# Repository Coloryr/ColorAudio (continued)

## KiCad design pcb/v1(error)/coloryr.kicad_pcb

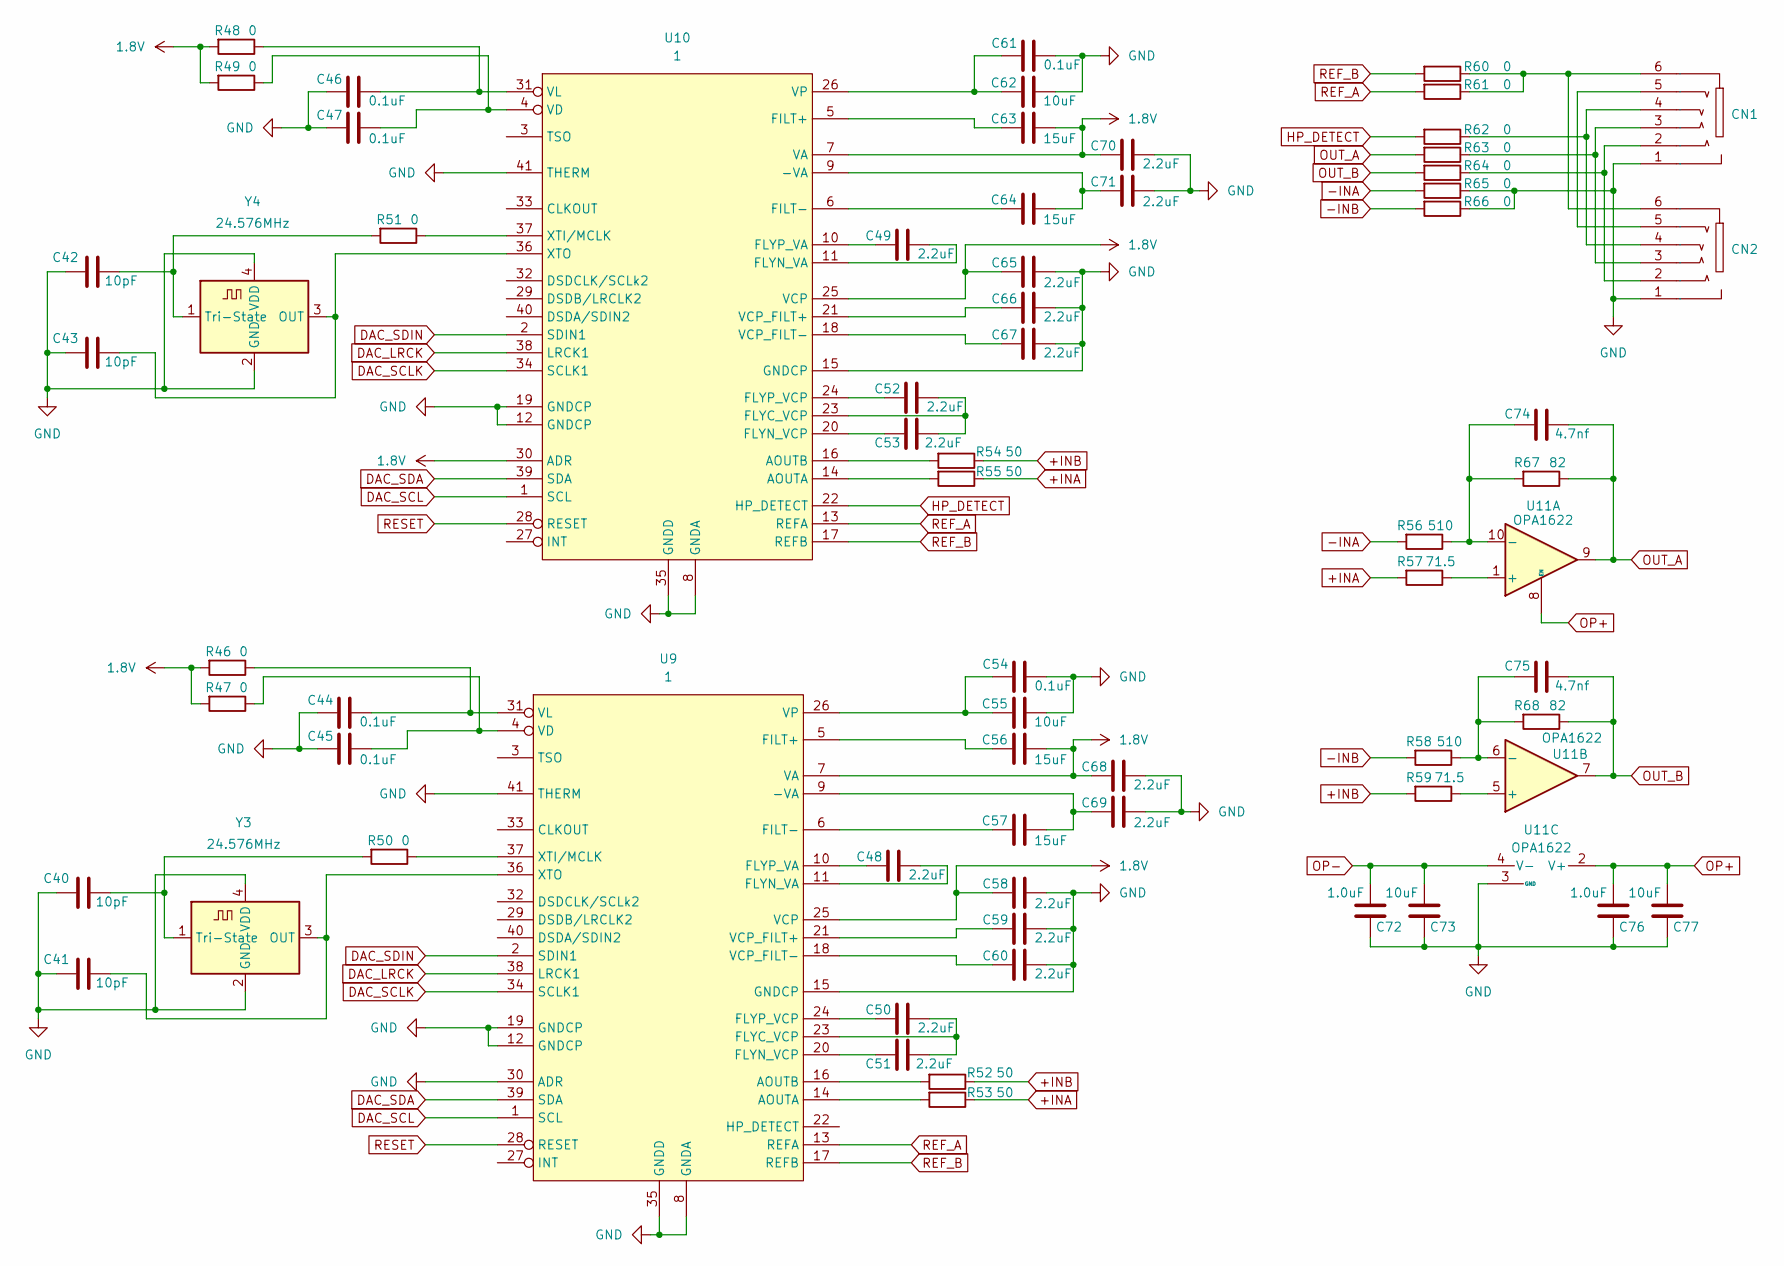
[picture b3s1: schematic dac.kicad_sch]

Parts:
C40, C41, C42, C43: 10pF; C_0402_1005Metric_Pad0.74x0.62mm_HandSolder
C44, C45, C46, C47, C54, C61: 0.1uF; C_0402_1005Metric_Pad0.74x0.62mm_HandSolder
C48, C49, C50, C51, C52, C53, C58, C59, C60, C65, C66, C67, C68, C69, C70, C71: 2.2uF; C_0402_1005Metric_Pad0.74x0.62mm_HandSolder
C55, C62, C73, C77: 10uF; C_0402_1005Metric_Pad0.74x0.62mm_HandSolder
C56, C57, C63, C64: 15uF; C_0402_1005Metric_Pad0.74x0.62mm_HandSolder
C72, C76: 1.0uF; C_0402_1005Metric_Pad0.74x0.62mm_HandSolder
C74, C75: 4.7nf; C_0805_2012Metric_Pad1.18x1.45mm_HandSolder
CN1: AUDIO-TH_PJ-3136-B
CN2: AUDIO-TH_PJ-625G
R46, R47, R48, R49, R50, R51: 0; R_0402_1005Metric_Pad0.72x0.64mm_HandSolder
R52, R53, R54, R55: 50; R_0805_2012Metric_Pad1.20x1.40mm_HandSolder
R56, R58: 510; R_0805_2012Metric_Pad1.20x1.40mm_HandSolder
R57, R59: 71.5; R_0805_2012Metric_Pad1.20x1.40mm_HandSolder
R60, R61, R62, R63, R64, R65, R66: 0; R_1206_3216Metric_Pad1.30x1.75mm_HandSolder
R67, R68: 82; R_0805_2012Metric_Pad1.20x1.40mm_HandSolder
U9, U10: 1; QFN-40-1EP_5x5mm_P0.4mm_EP3.6x3.6mm_ThermalVias
U11: OPA1622; Texas_S-PVSON-N10
Y3, Y4: 24.576MHz; Crystal_SMD_3225-4Pin_3.2x2.5mm_HandSoldering

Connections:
1.8V: C56.2, C58.2, C63.2, C65.2, C68.2, C70.2, R46.2, R47.2, R48.2, R49.2, U9.7 (VA), U9.25 (VCP), U10.7 (VA), U10.25 (VCP), U10.30 (ADR); also elsewhere on the board
+INA: R53.1, R55.1, R57.2
+INB: R52.1, R54.1, R59.2
-INA: R56.2, R65.2
-INB: R58.2, R66.2
DAC_LRCK: U9.38 (LRCK1), U10.38 (LRCK1); also elsewhere on the board
DAC_SCL: U9.1 (SCL), U10.1 (SCL); also elsewhere on the board
DAC_SCLK: U9.34 (SCLK1), U10.34 (SCLK1); also elsewhere on the board
DAC_SDA: U9.39 (SDA), U10.39 (SDA); also elsewhere on the board
DAC_SDIN: U9.2 (SDIN1), U10.2 (SDIN1); also elsewhere on the board
GND: C40.1, C41.1, C42.1, C43.1, C44.2, C45.2, C46.2, C47.2, C54.1, C55.2, C58.1, C59.1, C60.1, C61.1, C62.2, C65.1, C66.1, C67.1, C68.1, C69.1, C70.1, C71.1, C72.1, C73.1, C76.1, C77.1, CN1.1, CN2.1, R65.1, R66.1, U9.8 (GNDA), U9.12 (GNDCP), U9.15 (GNDCP), U9.19 (GNDCP), U9.30 (ADR), U9.35 (GNDD), U9.41 (THERM), U10.8 (GNDA), U10.12 (GNDCP), U10.15 (GNDCP), U10.19 (GNDCP), U10.35 (GNDD), U10.41 (THERM), U11.3 (GND), Y3.2 (GND), Y3.4 (VDD), Y4.2 (GND), Y4.4 (VDD); also elsewhere on the board
HP_DETECT: R62.2, U10.22 (HP_DETECT)
unnamed: CN1.4 (3), CN2.4 (3), R62.1
unnamed: CN1.2, CN2.2, R64.1
unnamed: CN1.3, CN2.3, R63.1
unnamed: CN1.5, CN2.5
unnamed: CN1.6, CN2.6, R60.1, R61.1
unnamed: C57.2, C69.2, U9.9 (-VA)
unnamed: R53.2, U9.14 (AOUTA)
unnamed: R52.2, U9.16 (AOUTB)
unnamed: C56.1, U9.5 (FILT+)
unnamed: C57.1, U9.6 (FILT-)
unnamed: C50.1, C51.1, U9.23 (FLYC_VCP)
unnamed: C48.1, U9.11 (FLYN_VA)
unnamed: C51.2, U9.20 (FLYN_VCP)
unnamed: C48.2, U9.10 (FLYP_VA)
unnamed: C50.2, U9.24 (FLYP_VCP)
unnamed: C59.2, U9.21 (VCP_FILT+)
unnamed: C60.2, U9.18 (VCP_FILT-)
unnamed: C45.1, R47.1, U9.4 (VD)
unnamed: C44.1, R46.1, U9.31 (VL)
unnamed: C54.2, C55.1, U9.26 (VP)
unnamed: R50.1, U9.37 (XTI/MCLK)
unnamed: C41.2, U9.36 (XTO), Y3.3 (OUT)
unnamed: C64.2, C71.2, U10.9 (-VA)
unnamed: R55.2, U10.14 (AOUTA)
unnamed: R54.2, U10.16 (AOUTB)
unnamed: C63.1, U10.5 (FILT+)
unnamed: C64.1, U10.6 (FILT-)
unnamed: C52.1, C53.1, U10.23 (FLYC_VCP)
unnamed: C49.1, U10.11 (FLYN_VA)
unnamed: C53.2, U10.20 (FLYN_VCP)
unnamed: C49.2, U10.10 (FLYP_VA)
unnamed: C52.2, U10.24 (FLYP_VCP)
unnamed: C66.2, U10.21 (VCP_FILT+)
unnamed: C67.2, U10.18 (VCP_FILT-)
unnamed: C47.1, R49.1, U10.4 (VD)
unnamed: C46.1, R48.1, U10.31 (VL)
unnamed: C61.2, C62.1, U10.26 (VP)
unnamed: R51.1, U10.37 (XTI/MCLK)
unnamed: C43.2, U10.36 (XTO), Y4.3 (OUT)
unnamed: R57.1, U11.1 (+)
unnamed: C74.2, R56.1, R67.2, U11.10 (-)
unnamed: R59.1, U11.5 (+)
unnamed: C75.2, R58.1, R68.2, U11.6 (-)
unnamed: C40.2, R50.2, Y3.1 (Tri-State)
unnamed: C42.2, R51.2, Y4.1 (Tri-State)
OP+: C76.2, C77.2, U11.2 (V+), U11.8 (EN); also elsewhere on the board
OP-: C72.2, C73.2, U11.4 (V-), U11.11 (V-); also elsewhere on the board
OUT_A: C74.1, R63.2, R67.1, U11.9
OUT_B: C75.1, R64.2, R68.1, U11.7
REF_A: R61.2, U9.13 (REFA), U10.13 (REFA)
REF_B: R60.2, U9.17 (REFB), U10.17 (REFB)
RESET: U9.28 (RESET), U10.28 (RESET); also elsewhere on the board

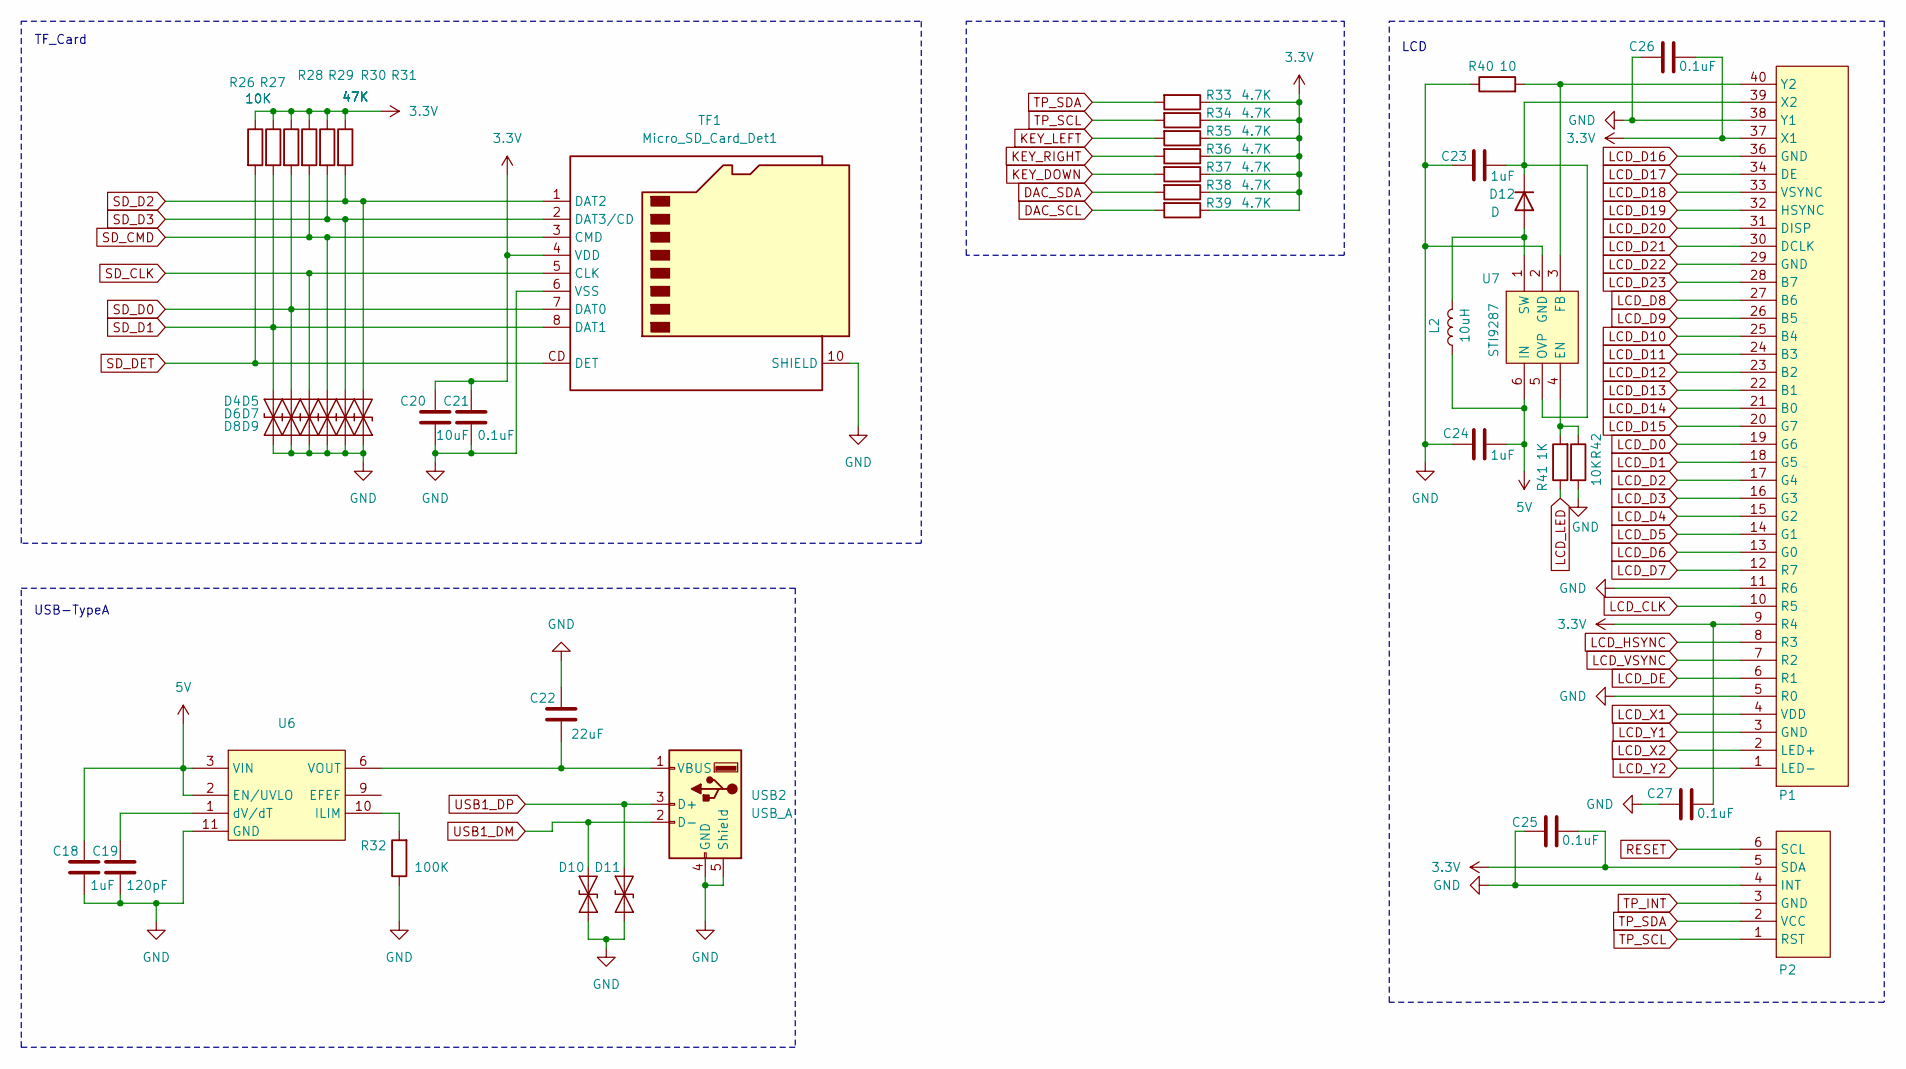
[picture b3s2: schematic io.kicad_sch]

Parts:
C18, C23, C24: 1uF; C_0402_1005Metric_Pad0.74x0.62mm_HandSolder
C19: 120pF; C_0402_1005Metric_Pad0.74x0.62mm_HandSolder
C20: 10uF; C_0402_1005Metric_Pad0.74x0.62mm_HandSolder
C21, C25, C26, C27: 0.1uF; C_0402_1005Metric_Pad0.74x0.62mm_HandSolder
C22: 22uF; C_0603_1608Metric_Pad1.08x0.95mm_HandSolder
D4, D5, D6, D7, D8, D9, D10, D11: ESD9B5.0ST5G; D_SOD-523
D12: D; D_SOD-323_HandSoldering
L2: 10uH; L_TDK_NLV25_2.5x2.0mm
P1: Hirose_FH12-40S-0.5SH_1x40-1MP_P0.50mm_Horizontal
P2: Hirose_FH12-6S-0.5SH_1x06-1MP_P0.50mm_Horizontal
R26, R27, R42: 10K; R_0402_1005Metric_Pad0.72x0.64mm_HandSolder
R28, R29, R30, R31: 47K; R_0402_1005Metric_Pad0.72x0.64mm_HandSolder
R32: 100K; C_0402_1005Metric_Pad0.74x0.62mm_HandSolder
R33, R34, R35, R36, R37, R38, R39: 4.7K; C_0402_1005Metric_Pad0.74x0.62mm_HandSolder
R40: 10; R_2512_6332Metric_Pad1.40x3.35mm_HandSolder
R41: 1K; R_0402_1005Metric_Pad0.72x0.64mm_HandSolder
TF1: Micro_SD_Card_Det1; TF-SMD_TF-PUSH
U6: TCKE812
U7: STI9287; SOT-23-6_Handsoldering
USB2: USB_A; USB-A-TH_AF-ZJWG

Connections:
3.3V: C20.1, C21.1, C25.2, C26.2, C27.2, P1.9 (R4), P1.37 (X1), P2.5 (SDA), R26.1, R27.1, R28.1, R29.1, R30.1, R31.1, R33.1, R34.1, R35.1, R36.1, R37.1, R38.1, R39.1, TF1.4 (VDD); also elsewhere on the board
5V: C18.1, C24.2, L2.1, U6.2 (EN/UVLO), U6.3 (VIN), U6.4 (VIN), U6.5 (VIN), U7.6 (IN); also elsewhere on the board
DAC_SCL: R39.2; also elsewhere on the board
DAC_SDA: R38.2; also elsewhere on the board
GND: C18.2, C19.2, C20.2, C21.2, C22.1, C23.2, C24.1, C25.1, C26.1, C27.1, D4.1 (A1), D5.1 (A1), D6.1 (A1), D7.1 (A1), D8.1 (A1), D9.1 (A1), D10.1 (A1), D11.1 (A1), P1.5 (R0), P1.11 (R6), P1.38 (Y1), P2.4 (INT), R32.1, R40.1, R42.2, TF1.6 (VSS), TF1.10 (SHIELD), TF1.11 (SHIELD), TF1.12 (SHIELD), TF1.13 (SHIELD), U6.11 (GND), U7.2 (GND), USB2.4 (GND), USB2.5 (Shield); also elsewhere on the board
KEY_DOWN: P2.3 (GND), R37.2; also elsewhere on the board
KEY_LEFT: R35.2; also elsewhere on the board
KEY_RIGHT: R36.2; also elsewhere on the board
LCD_CLK: P1.10 (R5); also elsewhere on the board
LCD_D0: P1.19 (G6); also elsewhere on the board
LCD_D1: P1.18 (G5); also elsewhere on the board
LCD_D2: P1.17 (G4); also elsewhere on the board
LCD_D3: P1.16 (G3); also elsewhere on the board
LCD_D4: P1.15 (G2); also elsewhere on the board
LCD_D5: P1.14 (G1); also elsewhere on the board
LCD_D6: P1.13 (G0); also elsewhere on the board
LCD_D7: P1.12 (R7); also elsewhere on the board
LCD_D8: P1.27 (B6); also elsewhere on the board
LCD_D9: P1.26 (B5); also elsewhere on the board
LCD_D10: P1.25 (B4); also elsewhere on the board
LCD_D11: P1.24 (B3); also elsewhere on the board
LCD_D12: P1.23 (B2); also elsewhere on the board
LCD_D13: P1.22 (B1); also elsewhere on the board
LCD_D14: P1.21 (B0); also elsewhere on the board
LCD_D15: P1.20 (G7); also elsewhere on the board
LCD_D16: P1.36 (GND); also elsewhere on the board
LCD_D17: P1.34 (DE); also elsewhere on the board
LCD_D18: P1.33 (VSYNC); also elsewhere on the board
LCD_D19: P1.32 (HSYNC); also elsewhere on the board
LCD_D20: P1.31 (DISP); also elsewhere on the board
LCD_D21: P1.30 (DCLK); also elsewhere on the board
LCD_D22: P1.29 (GND); also elsewhere on the board
LCD_D23: P1.28 (B7); also elsewhere on the board
LCD_DE: P1.6 (R1); also elsewhere on the board
LCD_HSYNC: P1.8 (R3); also elsewhere on the board
LCD_LED: R41.1; also elsewhere on the board
LCD_VSYNC: P1.7 (R2); also elsewhere on the board
LCD_X1: P1.4 (VDD); also elsewhere on the board
LCD_X2: P1.2 (LED+); also elsewhere on the board
LCD_Y1: P1.3 (GND); also elsewhere on the board
LCD_Y2: P1.1 (LED-); also elsewhere on the board
unnamed: D12.2 (A), L2.2, U7.1 (SW)
unnamed: C23.1, D12.1 (K), P1.39 (X2), U7.5 (OVP)
unnamed: P1.40 (Y2), R40.2, U7.3 (FB)
unnamed: R32.2, U6.10 (ILIM)
unnamed: C19.1, U6.1 (dV/dT)
unnamed: R41.2, R42.1, U7.4 (EN)
unnamed: C22.2, U6.6 (VOUT), U6.7 (VOUT), U6.8 (VOUT), USB2.1 (VBUS)
RESET: P2.6 (SCL); also elsewhere on the board
SD_CLK: D6.2 (A2), TF1.5 (CLK); also elsewhere on the board
SD_CMD: D7.2 (A2), R29.2, TF1.3 (CMD); also elsewhere on the board
SD_D0: D5.2 (A2), R28.2, TF1.7 (DAT0); also elsewhere on the board
SD_D1: D4.2 (A2), R27.2, TF1.8 (DAT1); also elsewhere on the board
SD_D2: D9.2 (A2), R31.2, TF1.1 (DAT2); also elsewhere on the board
SD_D3: D8.2 (A2), R30.2, TF1.2 (DAT3/CD); also elsewhere on the board
SD_DET: R26.2, TF1.CD (DET); also elsewhere on the board
TP_SCL: P2.1 (RST), R34.2; also elsewhere on the board
TP_SDA: P2.2 (VCC), R33.2; also elsewhere on the board
USB1_DM: D10.2 (A2), USB2.2 (D-); also elsewhere on the board
USB1_DP: D11.2 (A2), USB2.3 (D+); also elsewhere on the board

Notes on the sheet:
USB-TypeA
LCD
TF_Card

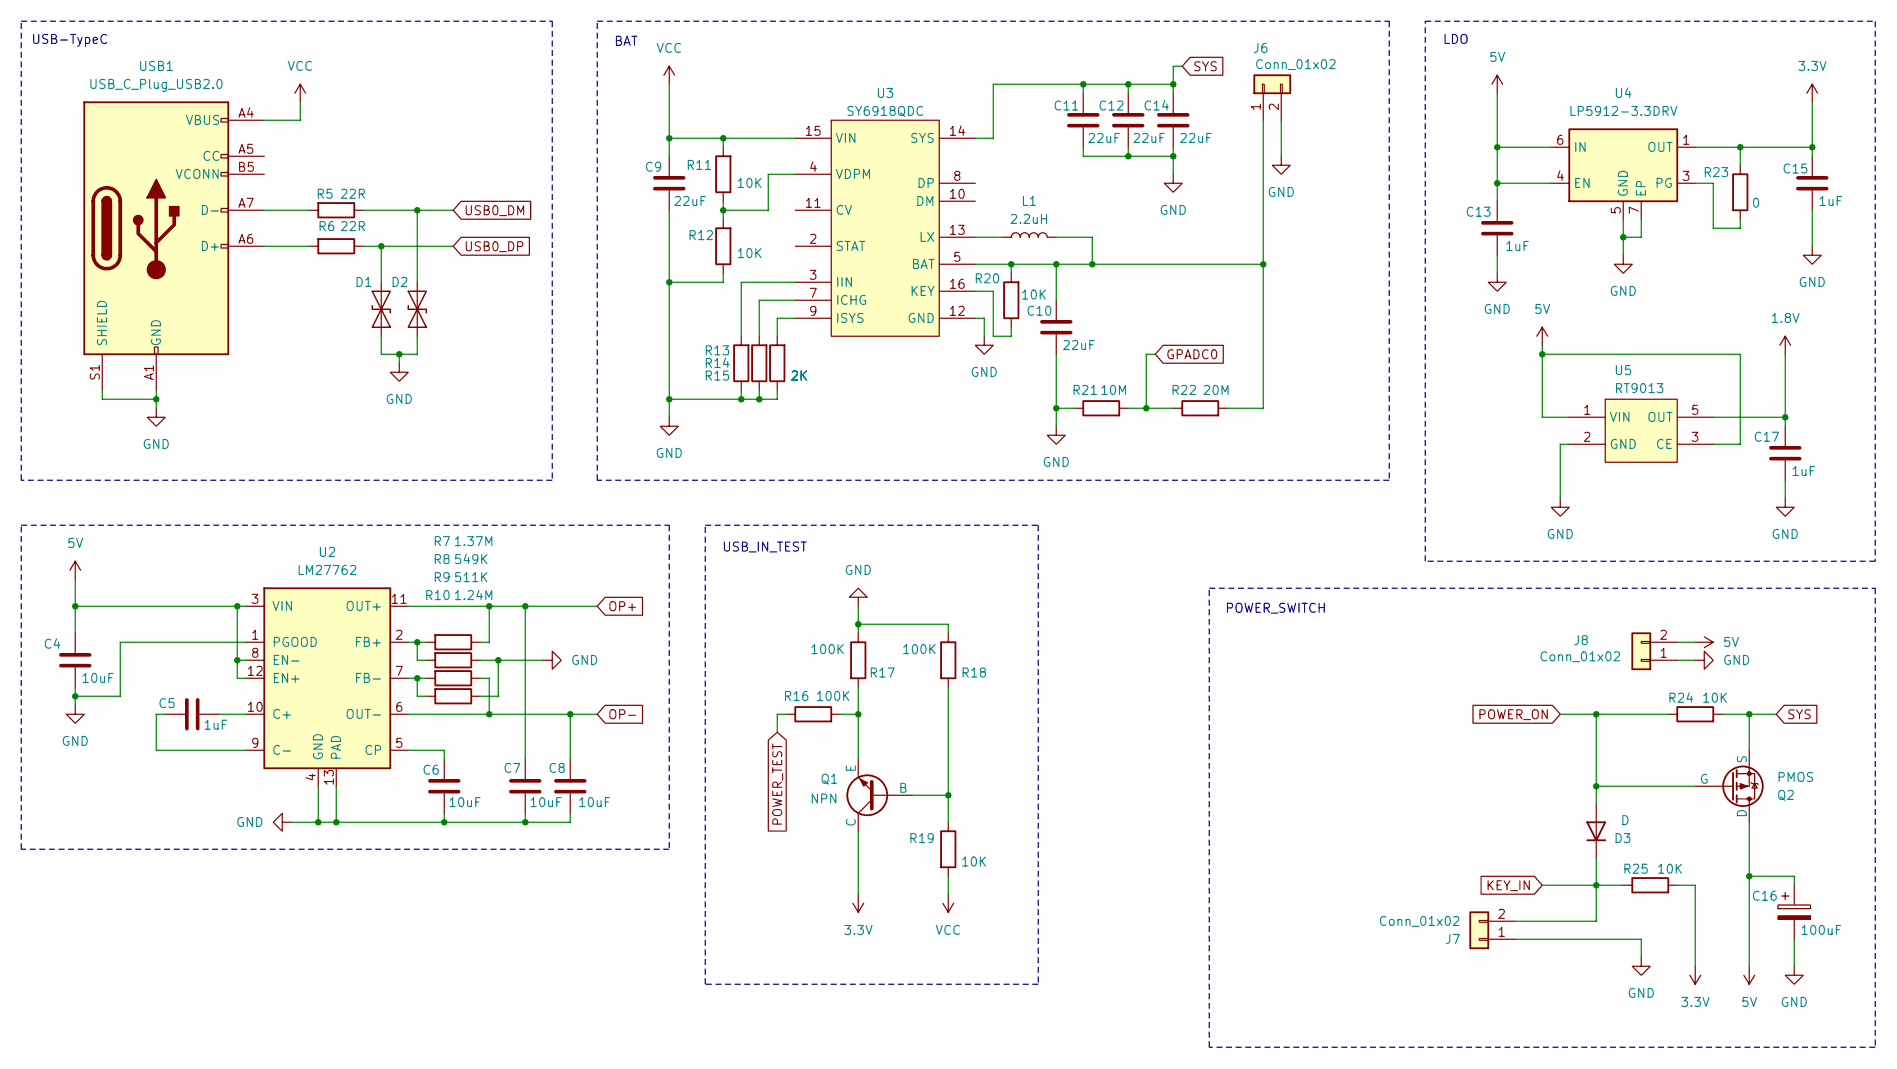
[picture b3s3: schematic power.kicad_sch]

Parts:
C4, C6, C7, C8: 10uF; C_0402_1005Metric_Pad0.74x0.62mm_HandSolder
C5, C13, C15, C17: 1uF; C_0402_1005Metric_Pad0.74x0.62mm_HandSolder
C9, C10, C11, C12, C14: 22uF; C_0603_1608Metric_Pad1.08x0.95mm_HandSolder
C16: 100uF; CP_EIA-3528-21_Kemet-B_Pad1.50x2.35mm_HandSolder
D1, D2: ESD9B5.0ST5G; D_SOD-523
D3: D; D_SOD-323_HandSoldering
J6, J8: Conn_01x02; PinHeader_1x02_P2.54mm_Vertical
J7: Conn_01x02; PinHeader_1x02_P2.00mm_Vertical
L1: 2.2uH; L_1008_2520Metric_Pad1.43x2.20mm_HandSolder
Q1: NPN; SOT-23
Q2: PMOS; SOT-23_Handsoldering
R5, R6: 22R; C_0402_1005Metric_Pad0.74x0.62mm_HandSolder
R7: 1.37M; C_0402_1005Metric_Pad0.74x0.62mm_HandSolder
R8: 549K; C_0402_1005Metric_Pad0.74x0.62mm_HandSolder
R9: 511K; C_0402_1005Metric_Pad0.74x0.62mm_HandSolder
R10: 1.24M; C_0402_1005Metric_Pad0.74x0.62mm_HandSolder
R11, R12, R19, R20: 10K; C_0402_1005Metric_Pad0.74x0.62mm_HandSolder
R13, R14, R15: 2K; C_0402_1005Metric_Pad0.74x0.62mm_HandSolder
R16, R17, R18: 100K; C_0402_1005Metric_Pad0.74x0.62mm_HandSolder
R21: 10M; R_0402_1005Metric_Pad0.72x0.64mm_HandSolder
R22: 20M; L_0402_1005Metric_Pad0.77x0.64mm_HandSolder
R23: 0; R_0402_1005Metric_Pad0.72x0.64mm_HandSolder
R24, R25: 10K; R_0402_1005Metric_Pad0.72x0.64mm_HandSolder
U2: LM27762; WSON-12-1EP_3x2mm_P0.5mm_EP1x2.65_ThermalVias
U3: SY6918QDC; SY6918
U4: LP5912-3.3DRV; WSON-6-1EP_2x2mm_P0.65mm_EP1x1.6mm_ThermalVias
U5: SOT-23-5_HandSoldering
USB1: USB_C_Plug_USB2.0; USB_C_Receptacle_GCT_USB4085

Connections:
1.8V: C17.1, U5.5 (OUT); also elsewhere on the board
3.3V: C15.1, Q1.3 (C), R23.1, R25.2, U4.1 (OUT); also elsewhere on the board
5V: C4.1, C13.1, C16.1, J8.2, Q2.3 (D), U2.3 (VIN), U2.8 (EN-), U2.12 (EN+), U4.4 (EN), U4.6 (IN), U5.1 (VIN), U5.3 (CE); also elsewhere on the board
GND: C4.2, C6.1, C7.1, C8.1, C9.2, C10.2, C11.2, C12.2, C13.2, C14.2, C15.2, C16.2, C17.2, D1.1 (A1), D2.1 (A1), J6.2, J7.1, J8.1, R8.1, R10.1, R12.1, R13.1, R14.1, R15.1, R17.1, R18.1, R21.1, U2.1 (PGOOD), U2.4 (GND), U2.13 (PAD), U3.12 (GND), U4.5 (GND), U4.7 (EP), U5.2 (GND), USB1.A1 (GND), USB1.A12 (GND), USB1.B1 (GND), USB1.B12 (GND), USB1.S1 (SHIELD); also elsewhere on the board
GPADC0: R21.2, R22.1; also elsewhere on the board
KEY_IN: D3.1 (K), J7.2, R25.1; also elsewhere on the board
unnamed: C10.1, J6.1, L1.2, R20.2, R22.2, U3.5 (BAT)
unnamed: Q1.1 (B), R18.2, R19.1
unnamed: Q1.2 (E), R16.2, R17.2
unnamed: R5.2, USB1.A7 (D-), USB1.B7 (D-)
unnamed: R6.2, USB1.A6 (D+), USB1.B6 (D+)
unnamed: C5.2, U2.10 (C+)
unnamed: C5.1, U2.9 (C-)
unnamed: C6.2, U2.5 (CP)
unnamed: R7.2, R8.2, U2.2 (FB+)
unnamed: R9.2, R10.2, U2.7 (FB-)
unnamed: R14.2, U3.7 (ICHG)
unnamed: R13.2, U3.3 (IIN)
unnamed: R15.2, U3.9 (ISYS)
unnamed: R20.1, U3.16 (KEY)
unnamed: L1.1, U3.13 (LX)
unnamed: R11.1, R12.2, U3.4 (VDPM)
unnamed: R23.2, U4.3 (PG)
OP+: C7.2, R7.1, U2.11 (OUT+); also elsewhere on the board
OP-: C8.2, R9.1, U2.6 (OUT-); also elsewhere on the board
POWER_ON: D3.2 (A), Q2.1 (G), R24.1; also elsewhere on the board
POWER_TEST: R16.1; also elsewhere on the board
SYS: C11.1, C12.1, C14.1, Q2.2 (S), R24.2, U3.14 (SYS)
USB0_DM: D2.2 (A2), R5.1; also elsewhere on the board
USB0_DP: D1.2 (A2), R6.1; also elsewhere on the board
VCC: C9.1, R11.2, R19.2, U3.15 (VIN), USB1.A4 (VBUS), USB1.A9 (VBUS), USB1.B4 (VBUS), USB1.B9 (VBUS)

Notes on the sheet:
USB_IN_TEST
POWER_SWITCH
LDO
BAT
USB-TypeC

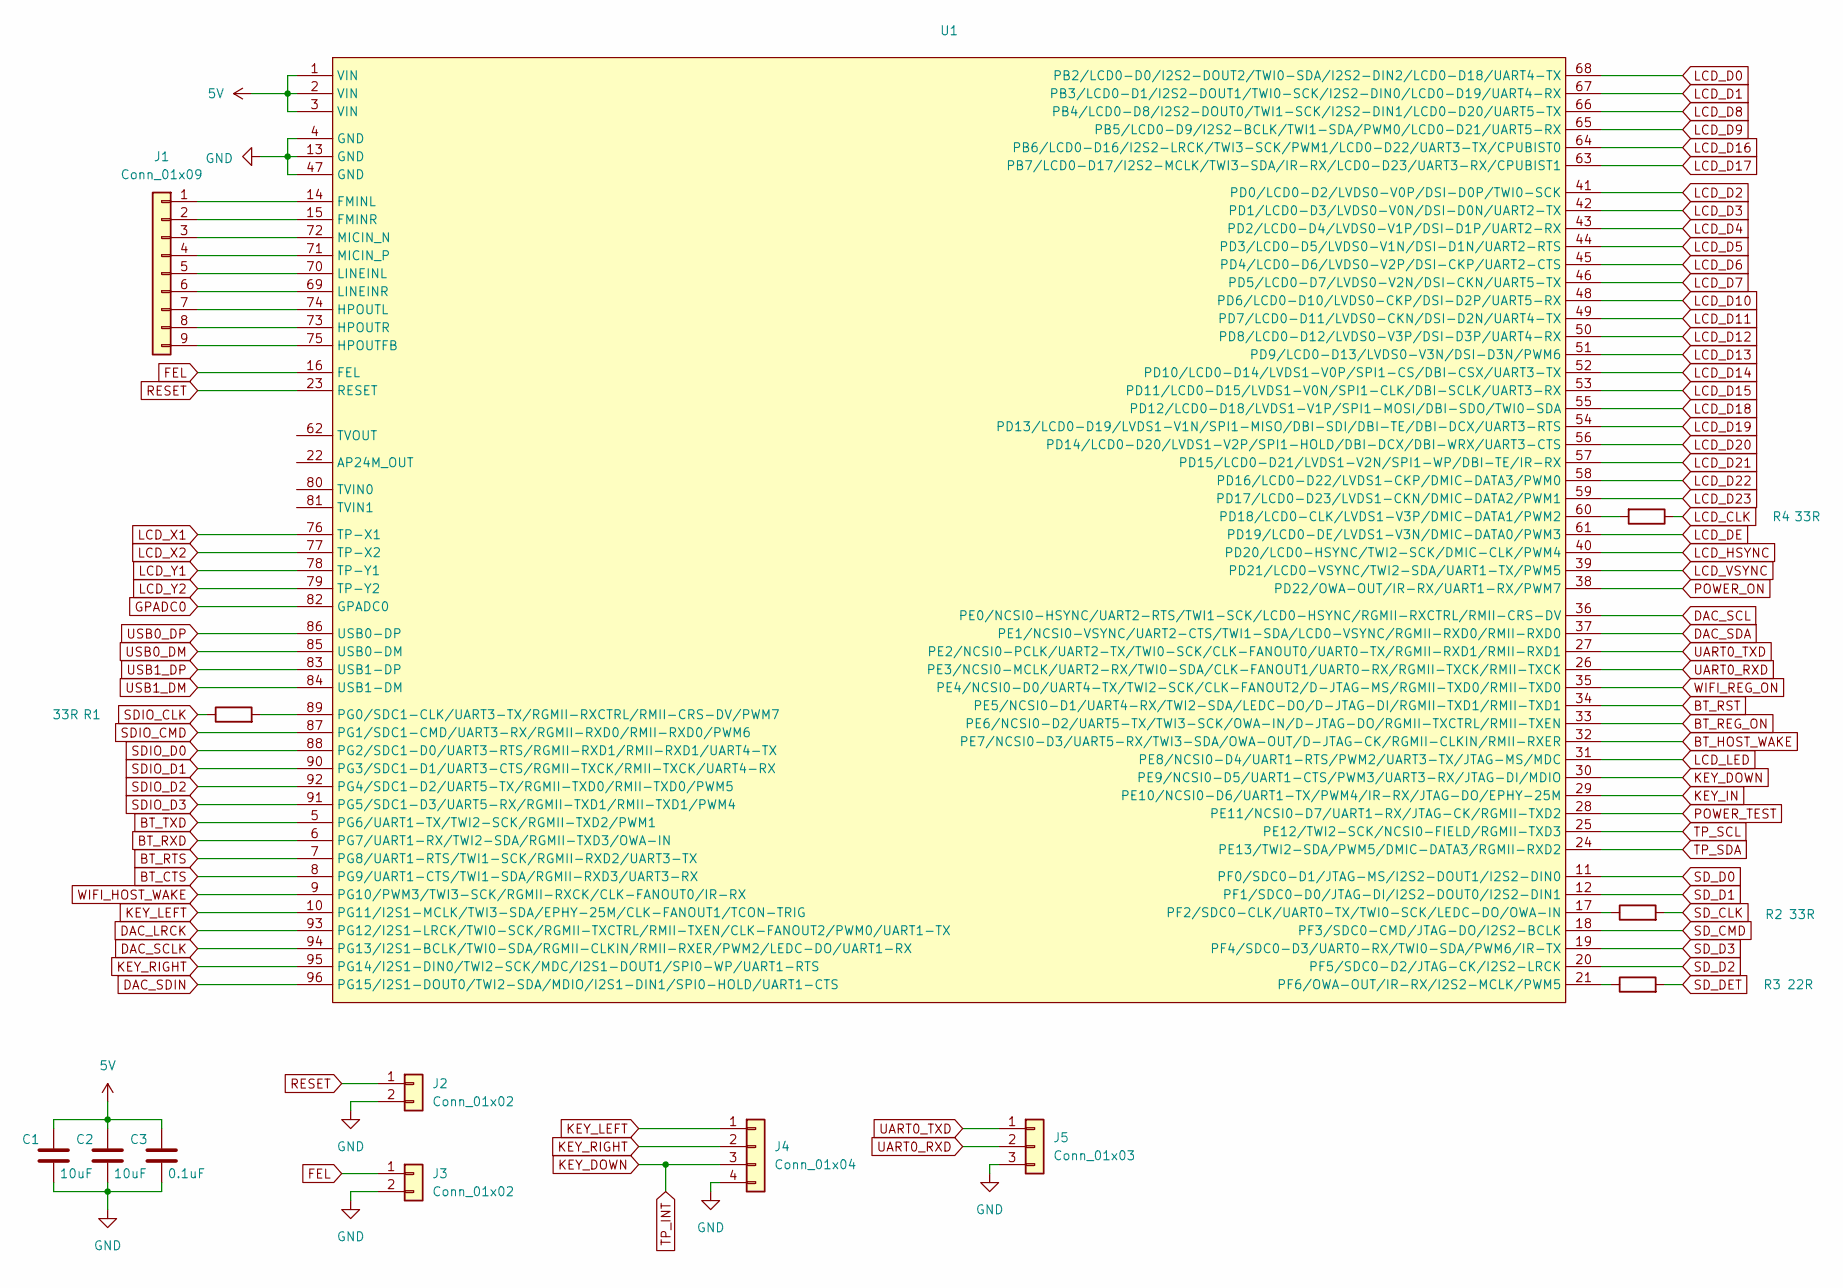
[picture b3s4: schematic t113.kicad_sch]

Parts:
C1, C2: 10uF; C_0402_1005Metric_Pad0.74x0.62mm_HandSolder
C3: 0.1uF; C_0402_1005Metric_Pad0.74x0.62mm_HandSolder
J1: Conn_01x09; PinHeader_1x09_P2.00mm_Vertical
J2, J3: Conn_01x02; PinHeader_1x02_P2.00mm_Vertical
J4: Conn_01x04; PinHeader_1x04_P2.00mm_Vertical
J5: Conn_01x03; PinHeader_1x03_P2.00mm_Vertical
R1, R4: 33R; C_0402_1005Metric_Pad0.74x0.62mm_HandSolder
R2: 33R; R_0402_1005Metric_Pad0.72x0.64mm_HandSolder
R3: 22R; R_0402_1005Metric_Pad0.72x0.64mm_HandSolder
U1: F133_CORE_V10

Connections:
5V: C1.1, C2.1, C3.1, U1.1 (VIN), U1.2 (VIN), U1.3 (VIN); also elsewhere on the board
BT_CTS: U1.8 (PG9/UART1-CTS/TWI1-SDA/RGMII-RXD3/UART3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); also elsewhere on the board
BT_HOST_WAKE: U1.32 (PE7/NCSI0-D3/UART5-RX/TWI3-SDA/OWA-OUT/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); also elsewhere on the board
BT_REG_ON: U1.33 (PE6/NCSI0-D2/UART5-TX/TWI3-SCK/OWA-IN/D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); also elsewhere on the board
BT_RST: U1.34 (PE5/NCSI0-D1/UART4-RX/TWI2-SDA/LEDC-DO/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); also elsewhere on the board
BT_RTS: U1.7 (PG8/UART1-RTS/TWI1-SCK/RGMII-RXD2/UART3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); also elsewhere on the board
BT_RXD: U1.6 (PG7/UART1-RX/TWI2-SDA/RGMII-TXD3/OWA-IN); also elsewhere on the board
BT_TXD: U1.5 (PG6/UART1-TX/TWI2-SCK/RGMII-TXD2/PWM1); also elsewhere on the board
DAC_LRCK: U1.93 (PG12/I2S1-LRCK/TWI0-SCK/RGMII-TXCTRL/RM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); also elsewhere on the board
DAC_SCL: U1.36 (PE0/NCSI0-HSYNC/UART2-RTS/TWI1-SCK/LCD0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); also elsewhere on the board
DAC_SCLK: U1.94 (PG13/I2S1-BCLK/TWI0-SDA/RGMII-CLKIN/RMI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); also elsewhere on the board
DAC_SDA: U1.37 (PE1/NCSI0-VSYNC/UART2-CTS/TWI1-SDA/LCD0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); also elsewhere on the board
DAC_SDIN: U1.96 (PG15/I2S1-DOUT0/TWI2-SDA/MDIO/I2S1-DIN1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); also elsewhere on the board
FEL: J3.1, U1.16 (FEL)
GND: C1.2, C2.2, C3.2, J2.2, J3.2, J4.4, J5.3, U1.4 (GND), U1.13 (GND), U1.47 (GND); also elsewhere on the board
GPADC0: U1.82 (GPADC0); also elsewhere on the board
KEY_DOWN: J4.3, U1.30 (PE9/NCSI0-D5/UART1-CTS/PWM3/UART3-RX/JT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); also elsewhere on the board
KEY_IN: U1.29 (PE10/NCSI0-D6/UART1-TX/PWM4/IR-RX/JTAG-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); also elsewhere on the board
KEY_LEFT: J4.1, U1.10 (PG11/I2S1-MCLK/TWI3-SDA/EPHY-25M/CLK-FA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); also elsewhere on the board
KEY_RIGHT: J4.2, U1.95 (PG14/I2S1-DIN0/TWI2-SCK/MDC/I2S1-DOUT1/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); also elsewhere on the board
LCD_CLK: R4.1; also elsewhere on the board
LCD_D0: U1.68 (PB2/LCD0-D0/I2S2-DOUT2/TWI0-SDA/I2S2-DI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); also elsewhere on the board
LCD_D1: U1.67 (PB3/LCD0-D1/I2S2-DOUT1/TWI0-SCK/I2S2-DI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); also elsewhere on the board
LCD_D2: U1.41 (PD0/LCD0-D2/LVDS0-V0P/DSI-D0P/TWI0-SCK); also elsewhere on the board
LCD_D3: U1.42 (PD1/LCD0-D3/LVDS0-V0N/DSI-D0N/UART2-TX); also elsewhere on the board
LCD_D4: U1.43 (PD2/LCD0-D4/LVDS0-V1P/DSI-D1P/UART2-RX); also elsewhere on the board
LCD_D5: U1.44 (PD3/LCD0-D5/LVDS0-V1N/DSI-D1N/UART2-RTS); also elsewhere on the board
LCD_D6: U1.45 (PD4/LCD0-D6/LVDS0-V2P/DSI-CKP/UART2-CTS); also elsewhere on the board
LCD_D7: U1.46 (PD5/LCD0-D7/LVDS0-V2N/DSI-CKN/UART5-TX); also elsewhere on the board
LCD_D8: U1.66 (PB4/LCD0-D8/I2S2-DOUT0/TWI1-SCK/I2S2-DI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); also elsewhere on the board
LCD_D9: U1.65 (PB5/LCD0-D9/I2S2-BCLK/TWI1-SDA/PWM0/LCD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); also elsewhere on the board
LCD_D10: U1.48 (PD6/LCD0-D10/LVDS0-CKP/DSI-D2P/UART5-RX); also elsewhere on the board
LCD_D11: U1.49 (PD7/LCD0-D11/LVDS0-CKN/DSI-D2N/UART4-TX); also elsewhere on the board
LCD_D12: U1.50 (PD8/LCD0-D12/LVDS0-V3P/DSI-D3P/UART4-RX); also elsewhere on the board
LCD_D13: U1.51 (PD9/LCD0-D13/LVDS0-V3N/DSI-D3N/PWM6); also elsewhere on the board
LCD_D14: U1.52 (PD10/LCD0-D14/LVDS1-V0P/SPI1-CS/DBI-CSX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); also elsewhere on the board
LCD_D15: U1.53 (PD11/LCD0-D15/LVDS1-V0N/SPI1-CLK/DBI-SC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); also elsewhere on the board
LCD_D16: U1.64 (PB6/LCD0-D16/I2S2-LRCK/TWI3-SCK/PWM1/LC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); also elsewhere on the board
LCD_D17: U1.63 (PB7/LCD0-D17/I2S2-MCLK/TWI3-SDA/IR-RX/L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); also elsewhere on the board
LCD_D18: U1.55 (PD12/LCD0-D18/LVDS1-V1P/SPI1-MOSI/DBI-S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); also elsewhere on the board
LCD_D19: U1.54 (PD13/LCD0-D19/LVDS1-V1N/SPI1-MISO/DBI-S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); also elsewhere on the board
LCD_D20: U1.56 (PD14/LCD0-D20/LVDS1-V2P/SPI1-HOLD/DBI-D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); also elsewhere on the board
LCD_D21: U1.57 (PD15/LCD0-D21/LVDS1-V2N/SPI1-WP/DBI-TE/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); also elsewhere on the board
LCD_D22: U1.58 (PD16/LCD0-D22/LVDS1-CKP/DMIC-DATA3/PWM0); also elsewhere on the board
LCD_D23: U1.59 (PD17/LCD0-D23/LVDS1-CKN/DMIC-DATA2/PWM1); also elsewhere on the board
LCD_DE: U1.61 (PD19/LCD0-DE/LVDS1-V3N/DMIC-DATA0/PWM3); also elsewhere on the board
LCD_HSYNC: U1.40 (PD20/LCD0-HSYNC/TWI2-SCK/DMIC-CLK/PWM4); also elsewhere on the board
LCD_LED: U1.31 (PE8/NCSI0-D4/UART1-RTS/PWM2/UART3-TX/JT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); also elsewhere on the board
LCD_VSYNC: U1.39 (PD21/LCD0-VSYNC/TWI2-SDA/UART1-TX/PWM5); also elsewhere on the board
LCD_X1: U1.76 (TP-X1); also elsewhere on the board
LCD_X2: U1.77 (TP-X2); also elsewhere on the board
LCD_Y1: U1.78 (TP-Y1); also elsewhere on the board
LCD_Y2: U1.79 (TP-Y2); also elsewhere on the board
unnamed: J1.1, U1.14 (FMINL)
unnamed: J1.2, U1.15 (FMINR)
unnamed: J1.3, U1.72 (MICIN_N)
unnamed: J1.4, U1.71 (MICIN_P)
unnamed: J1.5, U1.70 (LINEINL)
unnamed: J1.6, U1.69 (LINEINR)
unnamed: J1.7, U1.74 (HPOUTL)
unnamed: J1.8, U1.73 (HPOUTR)
unnamed: J1.9, U1.75 (HPOUTFB)
unnamed: R4.2, U1.60 (PD18/LCD0-CLK/LVDS1-V3P/DMIC-DATA1/PWM2)
unnamed: R2.1, U1.17 (PF2/SDC0-CLK/UART0-TX/TWI0-SCK/LEDC-DO/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)
unnamed: R3.1, U1.21 (PF6/OWA-OUT/IR-RX/I2S2-MCLK/PWM5)
unnamed: R1.2, U1.89 (PG0/SDC1-CLK/UART3-TX/RGMII-RXCTRL/RMII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)
POWER_ON: U1.38 (PD22/OWA-OUT/IR-RX/UART1-RX/PWM7); also elsewhere on the board
POWER_TEST: U1.28 (PE11/NCSI0-D7/UART1-RX/JTAG-CK/RGMII-TX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); also elsewhere on the board
RESET: J2.1, U1.23 (RESET); also elsewhere on the board
SDIO_CLK: R1.1; also elsewhere on the board
SDIO_CMD: U1.87 (PG1/SDC1-CMD/UART3-RX/RGMII-RXD0/RMII-R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); also elsewhere on the board
SDIO_D0: U1.88 (PG2/SDC1-D0/UART3-RTS/RGMII-RXD1/RMII-R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); also elsewhere on the board
SDIO_D1: U1.90 (PG3/SDC1-D1/UART3-CTS/RGMII-TXCK/RMII-T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); also elsewhere on the board
SDIO_D2: U1.92 (PG4/SDC1-D2/UART5-TX/RGMII-TXD0/RMII-TX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); also elsewhere on the board
SDIO_D3: U1.91 (PG5/SDC1-D3/UART5-RX/RGMII-TXD1/RMII-TX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); also elsewhere on the board
SD_CLK: R2.2; also elsewhere on the board
SD_CMD: U1.18 (PF3/SDC0-CMD/JTAG-DO/I2S2-BCLK); also elsewhere on the board
SD_D0: U1.11 (PF0/SDC0-D1/JTAG-MS/I2S2-DOUT1/I2S2-DIN0); also elsewhere on the board
SD_D1: U1.12 (PF1/SDC0-D0/JTAG-DI/I2S2-DOUT0/I2S2-DIN1); also elsewhere on the board
SD_D2: U1.20 (PF5/SDC0-D2/JTAG-CK/I2S2-LRCK); also elsewhere on the board
SD_D3: U1.19 (PF4/SDC0-D3/UART0-RX/TWI0-SDA/PWM6/IR-TX); also elsewhere on the board
SD_DET: R3.2; also elsewhere on the board
TP_SCL: U1.25 (PE12/TWI2-SCK/NCSI0-FIELD/RGMII-TXD3); also elsewhere on the board
TP_SDA: U1.24 (PE13/TWI2-SDA/PWM5/DMIC-DATA3/RGMII-RXD2); also elsewhere on the board
UART0_RXD: J5.2, U1.26 (PE3/NCSI0-MCLK/UART2-RX/TWI0-SDA/CLK-FA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)
UART0_TXD: J5.1, U1.27 (PE2/NCSI0-PCLK/UART2-TX/TWI0-SCK/CLK-FA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)
USB0_DM: U1.85 (USB0-DM); also elsewhere on the board
USB0_DP: U1.86 (USB0-DP); also elsewhere on the board
USB1_DM: U1.84 (USB1-DM); also elsewhere on the board
USB1_DP: U1.83 (USB1-DP); also elsewhere on the board
WIFI_HOST_WAKE: U1.9 (PG10/PWM3/TWI3-SCK/RGMII-RXCK/CLK-FANOU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); also elsewhere on the board
WIFI_REG_ON: U1.35 (PE4/NCSI0-D0/UART4-TX/TWI2-SCK/CLK-FANO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); also elsewhere on the board
